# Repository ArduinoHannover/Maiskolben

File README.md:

# Maiskolben

## SMD Lötstation, kompatibel zu Weller-Lötspitzen

Weller baut seit Jahren *die* Lötstationen für den professionellen Bereich.
Die WMRP/WXRP-Stationen heben sich durch ihre aktiven Lötspitzen von anderen Produkten ab.
Mit einer außergewöhnlich kurzen Aufheizzeit im Sekundenbereich, einer direkt in der Spitze integrierten Temperaturmessung und dementsprechend schnelle Nachregulierung in Sekundenbruchteilen sind die Spitzen in der Industrie äußerst beliebt.
Die Spitzen selbst sind für 40€ im Handel erhältlich, die original Weller-Station kostet an die 600€.
Für den einfachen Maker oder Hobbyist auf keinen Fall ein Produkt, das beim Onlineshopping ohne weitere Überlegungen in den Warenkorb wandert.
Der *Maiskolben* hingegen ist eine erschwingliche Lösung für lediglich 40€, mit der die Spitzen ebenso angesteuert werden können.

* Betrieb mit 12V Netzteil (oder bis zu 24V mit Fertigplatine) oder 3s LiPo (Modellbau-Akku)
* Spannungsüberwachung (bei Akku für alle 3 Zellen und automatische Abschaltung bei zu geringer Ladung)
* Einfaches Wechseln von Spitzen mittels Klinken-Buchse/-Kabel
* 3 individuelle Temperatur-Presets
* Temperaturbereich von 200-450°C
* Gut ablesbares Farbdisplay mit allen nötigen Informationen
* Auto-Standby (entweder sensor- oder zeitgesteuert auf 150°C)
* Auto-Wakeup (entweder sensorgesteuert oder durch Berühren von Lötschwamm, Messingwolle oder Lötstelle)
* USB-Schnittstelle zur Überwachung oder Steuerung mittels PC
* Potentialausgleich-/ESD-Buchse (über 1MΩ an GND)
* Optisches Feedback der Heizleistung durch LED
* Open-Source-Software auf Basis von Arduino
* Software-Update kann per USB eingespielt werden

*Zu erwerben bei [HannIO](https://hannio.org).*

## Stromzufuhr

Die Stromzufuhr wird wahlweise über die Hohlstecker-Buchse (10-24V) *ODER* die JST-XH4 (11,1V) Buchse angeschlossen.
Bei Versionen < 3.0 niemals beide gleichzeitig anschließen!
Der Lötkolben (Weller RT-XX, z.B. RT-1 für feine Lötarbeiten) wird über die Klinkenbuchse mit einer Verlängerung angesteckt.

## Display

Das Display zeigt mittig in weißer Schrift die Soll-Temperatur, darunter, sofern eine Spitze eingesteckt ist, die aktuelle Ist-Temperatur.
Bei eingeschaltetem Lötkolben erscheint zusätzlich noch die Zeit, nach der sich der Lötkolben automatisch in den Standby versetzt.
Der Balken am oberen Bildschirmrand spiegelt die Ist-Temperatur wieder.
Oben Links wird die Spannung bzw. die Ladezustände der einzelnen Zellen angezeigt.
Links wird durch das Power-Symbol der aktuelle Zustand (aus = rot, Standby = gelb, an = grün) signalisiert.
Am unteren Rand sind die drei Presets zu sehen.

## Bedienung

Nach dem Anstecken von Netzteil und Lötspitze kann die Station durch halten der Power-Taste (unten rechts) eingeschaltet werden.
Basierend auf der letzten Einstellung wird die angezeigte Soll- (Power-Symbol grün) oder die Standby-Temperatur (Symbol gelb) angefahren.

Mittels der Tasten rechts vom Display (Pfeile) lässt sich die Soll-Temperatur nach oben und unten korrigieren.
Sollte einer der Pfeile auf dem Display ausgegraut sein, so lässt sich über diese Temperatur hinaus keine weitere Änderung mehr vornehmen (200 ≥ T ≥ 450).

### Presets

Mittels der Preset-Tasten unter dem Bildschirm lassen sich voreingestellte Temperaturen als Soll-Temperatur setzen und die Station gleichzeitig aus dem Standby aufwecken.
Durch Gedrückthalten einer der drei Tasten wird der dort gespeicherte Wert durch die aktuelle Soll-Temperatur überschrieben.
Wird die Power-Taste nur kurz gedrückt, so wird der Standby-Zustand umgeschaltet.

### Startmenü

Es gibt ein verstecktes Menü, in dem sich der automatische Standby abschalten und ein automatisches Hochfahren auf die zuletzt gewählte Temperatur bei Spannungsversorgung aktiviert werden können. Um in dieses Menü zu gelangen, muss beim Anlegen der Spannungsversorgung während des Blinkens der LED die Power-Taste betätigt werden.

## Fehlermeldungen

#### USB power only/Connect power supply; Power too low/Connect power >5V
Die Lötstation wird entweder nur über USB oder eine Spannungsquelle mit knapp 5V versorgt.
Zum Betrieb wird ein adäquates Netzteil oder Akku benötigt (≥40W)

#### NO TIP; No tip connected/Tip slipped out?
Es wurde keine Spitze eingesteckt oder nicht erkannt.
Es kann sein, dass die Spitze defekt ist oder nicht richtig in der Buchse steckt.

#### Temperature dropped/Tip slipped out?
Es wurde ein zu großer Temperaturabfall bemerkt und die Wahrscheinlichkeit besteht, dass die Spitze leicht aus der Buchse herausgerutscht ist.
Durch das Herausrutschen kann eine Verbindung zwischen Masse und dem Sensor hergestellt werden, sodass die erkannte Temperatur beim Offset von 24°C liegt.

#### Not heating/Weak power source or short
Entweder kann die Stromversorgung nicht genug Leistung bringen, um die Spitze in einem angemessenen Zeitraum aufzuheizen oder es liegt wie bei obigem Fehler ein Kurzschluss von Masse und Sensor vor.

#### Battery low/Replace or charge
Der Akku hat auf mindestens einer Zelle eine zu geringe Spannung und sollte ersetzt oder geladen werden.

Fehlermeldungen müssen durch OK bestätigt werden.
Die Fehlermeldungen können nicht unterdrückt werden, sollte allerdings mehrfach hintereinander eine Meldung bestätigt und die Station wieder eingeschaltet werden, kann dies zu übermäßigem Erwärmen der Lötspitze führen.

## Software-Update

Um die aktuellste Software auf den Maiskolbe zu übertragen, muss zunächst die [Arduino-IDE](https://www.arduino.cc/en/Main/Software) heruntergeladen werden.
In diesem Repository befinden sich zwei Programme, zum einen Maiskolben_LCD für die Hardware-Revision 1.0 und Maiskolben_TFT für Hardware-Revisionen ab 1.5.
Die .ino Datei kann mit Arduino geöffnet werden.
Der Serielle-Port muss nach Herstellen einer Verbindung zwischen Maiskolben und PC unter _Werkzeuge_ > _Port_ ausgewählt werden.
Unter Umständen muss zuvor noch der [CH340 Treiber](http://www.wch.cn/download/CH341SER_ZIP.html) für den USB-Seriell-Wandler installiert werden.
Als _Board_ sollte _Arduino Nano_ mit _Prozessor: ATmega328 (Old Bootloader)_ ausgewählt werden.
Über _Sketch_ > _Hochladen_ bzw. den Pfeil nach Rechts in der oberen Leiste kann das Programm übertragen werden.

### Bibliotheken

Unter Umständen müssen vorher folgende Libraries noch über _Sketch_ > _Bibliothek einbinden_ > _.ZIP Bibliothek hinzufügen..._ eingebunden werden:

* [TimerOne](https://github.com/PaulStoffregen/TimerOne)
* [PID_v1](https://github.com/br3ttb/Arduino-PID-Library/)
* ~~[Adafruit_ST7735](https://github.com/adafruit/Adafruit-ST7735-Library)~~ (Software Version < 3.0)
* [TFT_ILI9163C](https://github.com/ArduinoHannover/TFT_ILI9163C)
* [Adafruit_GFX](https://github.com/adafruit/Adafruit-GFX-Library)

Dafür muss von den entsprechenden Seiten zuvor die ZIP heruntergeladen werden.
Diese kann dann in dem Dateibrowser, der sich nach obiger Anleitung öffnet, selektiert werden.

### Changelog

* 3.1
  * Option im Menü eingebaut, um zwischen Fahrenheit und Celsius zu wechseln
  * Bug behoben, der bei falsch initialisiertem EEPROM die Temperaturberechnung nicht richtig ausgeführt hat
* 3.0
  * Geänderte Display-Bibliothek (vgl. [Abschnitt Bibliotheken](#Bibliotheken))
  * Mehr Strings im Flash statt im RAM
  * Anpassungen um einen Maiskolben V3.2 im LiPo-Betrieb vollständig abzuschalten
  * Limitierung der Minimaltemperatur auf 200°C
  * `°C` wird mit bei Soll- und Ist-Temperatur angezeigt
  * Interne Temperatur-Kalibrierung für jeden Maiskolben individuell (bisher nur für Kalibrierung ab Werk)
* 2.8
  * Zeilenhöhe des Balkens ist nun variabel
  * Temperaturen als `#define` gesetzt
  * Temperaturberechnung wieder angepasst
  * EEPROM-Fehler behoben
* 2.7
  * TFT-Reset eingebaut
* 2.6
  * Schreibfehler korrigiert
  * Anpassungen an unterschiedliche Hardwareausführungen verbessert
  * Beim Aufruf des Menüs kommt man nach schließen direkt zum Programm
  * Autopower verfeinert
* 2.5
  * Interne Testroutinen hinzugefügt
  * Anpassung an Hardwarerevision ≥ 3.0
  * Wattanzeige hinzugefügt
* 2.4
  * Spannungsanzeige gegen Steckersymbol getauscht
* 2.3
  * Anpassung an unterschiedliche Display-Treiber (BGR/RGB)
  * Geänderte Temperaturmessung
* 2.1
  * Bidirektionale Steuerung über serielle Schnittstelle
* 2.0
  * Initiale Version für GitHub (TFT)
  * Auto-Standby hinzugefügt
  * Parameter angepasst

### Achtung!

Zur eigenen Sicherheit vor einem Software-Update die Lötspitze entfernen.
Zwar wird die Heizspannung beim Übertragen deaktiviert, dennoch kann es vereinzelt zu Fehlfunktionen und dadurch bedingtem unbeschränkten Aufheizen der Spitze kommen.

Modifikationen an der Software sind auf eigene Gefahr des Nutzers.

## Umbauten

Nachfolgend werden Modifikationen beschrieben, die die Funktionen des Maiskolben erweitern.
Für eigens durchgeführte Änderungen kann keine Haftung übernommen werden.

### Ablage-Sensor nachrüsten

Statt des automatischen Standbys nach einer bestimmten Zeit kann auch der Standby durch einen Ablage-Sensor erzwungen werden.
Auf der Platine befinden sich Kontakte mit STBY, 5V und GND.
Um den Standby zu aktivieren muss STBY mit GND verbunden werden, um wieder aufzuwachen muss die Verbindung getrennt werden.
Das Schalten von STBY nach GND kann entweder durch einen Schalter erfolgen, der beim auflegen der Spitze auslöst, alternativ mit einem Hall- oder Reed-Sensor.
Für letzteres muss an dem Ende des Klinken-Kabels, an dem die Spitze eingesteckt wird, ein Magnet angebracht werden, der den Sensor dann auslöst.

### Stromversorgungs-Schalter

Ab Hardware-Revision 1.5 gibt es auf der Platinenunterseite eine Lötbrücke mit der Beschriftung ON/OFF.
Bis einschließlich Revision 1.9 wird beim Durchtrennen dieser Brücke die gesamte Stromversorgung unterbrochen.
Ab Revision 1.11 wird hingegen nur noch die Zuleitung des LiPos getrennt.
An den beiden Lötpunkten können nach dem Durchtrennen der Leiterbahn Kabel zu einem Schalter gelötet werden, mit dem sich die Stromversorgung unterbrechen lässt.

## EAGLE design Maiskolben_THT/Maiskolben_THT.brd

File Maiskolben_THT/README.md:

# Maiskolben-Selfmade

## Selbstbau-Version des Maiskolben mit THT-Bauteilen

Die in diesem Ordner abgelegten Dateien sind für den Nachbau des Maiskolben mit THT-Bauteilen für die Make 5/16.

### Bauteile

| Menge | Bauteil |
---: | ---
1 | 2N700
1 | IRF5305
1 | OPA703PA (OPA336PA)
1 | 74HC4050
1 | Arduino Nano (o.vgl.)
1 | LED 5mm
1 | 220Ω (oder anderer passender Vorwiderstand für die LED)
1 | 100Ω
1 | 1kΩ
2 | 5k6Ω
5 | 10kΩ
1 | 68kΩ
1 | 100kΩ
1 | 10MΩ
2 | 100nF
2 | 10nF
ggf. | Buchsenleisten nach Bedarf
6 | Taster 6x6mm; möglichst hoch (12mm)
1 | Stereo Klinkenbuchse (EBS 35)
1 | DC Buchse (Netzteilspezifisch etwa Lumberg NEB21R)
1 | Passendes Netzteil
1 | Weller Lötspitze

Ein Großteil der Bauteile sind beim Elektronikeinzelhandel verfügbar, das Display hingegen fast ausschließlich bei [eBay](http://sndstrm.de/18tft) bestellbar (sofern nicht mehr verfügbar nach `1.8 tft` suchen, blaue Platine, **nicht** Adafruit), die [Platine oder das ganze Set kann ebenfalls online bestellt werden](https://hannio.org/produkt/maiskolben-tht/).

## Aufbau

Der MOSFET (IRF5305) kann unter das Display gebogen werden, dazu vorher etwas mit Klebeband isolieren, um Kontakt zu vermeiden. Den 2N7000 dafür weit genug versenken.

## Software

Für die Software bitte [die Update-Anleitung](https://github.com/ArduinoHannover/Maiskolben#software-update) zur Hilfe nehmen.

## Problembehandlung

### Display bleibt weiß
In diesem Fall arbeitet der Reset vom Display nicht sauber. Softwareseitig ist dafür `#define USE_TFT_RESET` vorgesehen. Um einen Reset vom Arduino zu triggern, muss allerdings die Reset-Leitung zwischen Arduino und Display getrennt werden.

Bei neueren Platinen gibt es dafür einen Jumper `R A` - dieser ist standardmäßig an R (Reset) angeschlossen. Diese Verbindung muss etwa mit einem Cutter aufgetrennt werden und dann eine Brücke an `A` gesetzt werden.

Ansonsten muss die Leiterbahn aufgekratzt werden oder brutal der Reset-Pin am Arduino weggeknipst werden. Dann muss die Leiterbahn zum Display mit A0 vom Arduino verbunden werden.

### Display zeigt Artefakte
Teilweise arbeitet der Spannungsregler nicht zufriedenstellend, sodass der Treiber des TFT ab und zu Spikes bekommt. In diesem Fall sollten verschiedene Kondensatoren (100nF sollte klappen) am Display VCC/GND oder auch zwischen GND und 5V ein größerer Kondensator (100uF/6,3V) eingebaut werden.

### Andere Probleme

[Fehlermeldungen](https://github.com/ArduinoHannover/Maiskolben#fehlermeldungen)

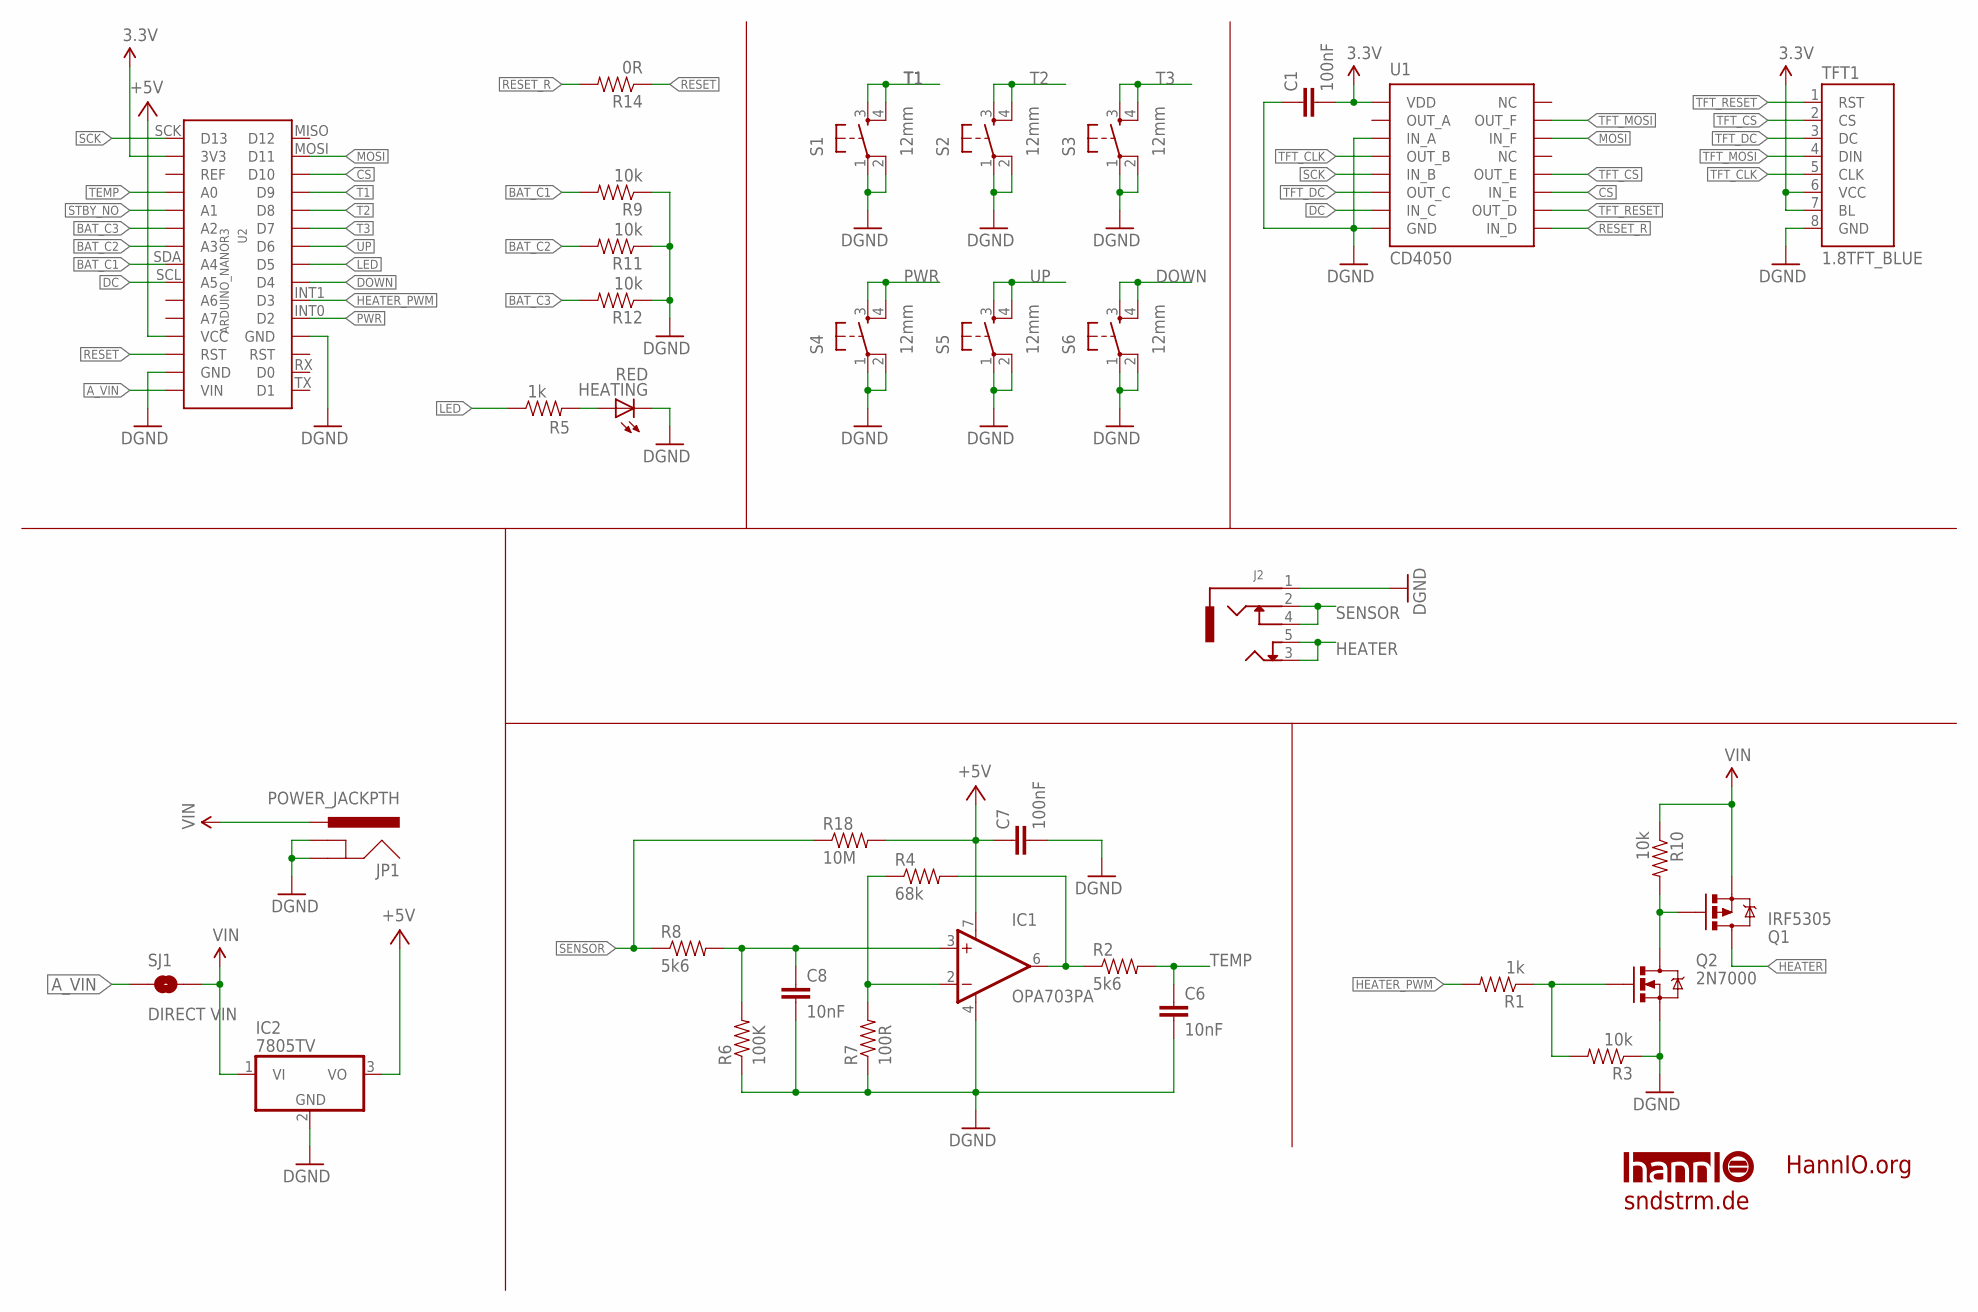
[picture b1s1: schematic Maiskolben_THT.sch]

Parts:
C1, C7: 100nF; CAP-PTH-SMALLEZ
C6, C8: 10nF; CAP-PTH-SMALLEZ
HEATING: RED; LED5MM
IC1: OPA703PA; DIL08
IC2: 7805TV; TO220V
J2: AUDIO_JACK_5PEBS_35; EBS_35
JP1: POWER_JACKPTH; POWER_JACK_PTH
Q1: IRF5305; TO220V
Q2: 2N7000; TO-92
R1, R5: 1k; AXIAL-0.3
R2, R8: 5k6; AXIAL-0.3
R3, R9, R10, R11, R12: 10k; AXIAL-0.3
R4: 68k; AXIAL-0.3
R6: 100K; AXIAL-0.3
R7: 100R; AXIAL-0.3
R14: 0R; AXIAL-0.3
R18: 10M; AXIAL-0.3
S1, S2, S3, S4, S5, S6: 12mm; TACTILE-PTH
SJ1: DIRECT VIN; PAD-JUMPER-2-NO_YES_SILK
TFT1: 1.8TFT_BLUE
U1: CD4050DIP16; CD4050
U2: ARDUINO_NANOR3; ARDUINO-NANO
U$1: HANNIO_MEDIUM

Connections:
3.3V: C1.2, TFT1.6 (VCC), TFT1.7 (BL), U1.VDD, U2.3V3
+5V: C7.1, IC1.7 (V+), IC2.3 (VO), R18.P$2 (2), U2.VCC
A_VIN: SJ1.1, U2.VIN
BAT_C1: R9.P$2 (2), U2.SDA (A4)
BAT_C2: R11.P$2 (2), U2.A3
BAT_C3: R12.P$2 (2), U2.A2
CS: U1.IN_E, U2.D10
DC: U1.IN_C, U2.SCL (A5)
DGND: C1.1, C6.2, C7.2, C8.2, HEATING.K (C), IC1.4 (V-), IC2.2 (GND), J2.1 (GND), JP1.GND, JP1.GNDBREAK, Q2.1 (S), R3.P$1 (1), R6.P$1 (1), R7.P$1 (1), R9.P$1 (1), R11.P$1 (1), R12.P$1 (1), S1.1, S1.2, S2.1, S2.2, S3.1, S3.2, S4.1, S4.2, S5.1, S5.2, S6.1, S6.2, TFT1.8 (GND), U1.GND, U1.IN_A, U2.GND@1 (GND), U2.GND@2 (GND)
DOWN: S6.3, S6.4, U2.D4
HEATER: J2.3 (TIP), J2.5 (TIP_NC), Q1.2 (D)
HEATER_PWM: R1.P$2 (2), U2.INT1 (D3)
HEAT_LED: HEATING.A, R5.P$2 (2)
LED: R5.P$1 (1), U2.D5
MOSI: U1.IN_F, U2.MOSI (D11)
unnamed: Q2.2 (G), R1.P$1 (1), R3.P$2 (2)
OPA+: C8.1, IC1.3 (+IN), R6.P$2 (2), R8.P$2 (2)
OPA-: IC1.2 (-IN), R4.P$1 (1), R7.P$2 (2)
OPA_OUT: IC1.6 (OUT), R2.P$1 (1), R4.P$2 (2)
PMOS_IN: Q1.1 (G), Q2.3 (D), R10.P$2 (2)
PWR: S4.3, S4.4, U2.INT0 (D2)
RESET: R14.P$1 (1), U2.RST@2 (RST)
RESET_R: R14.P$2 (2), U1.IN_D
SCK: U1.IN_B, U2.SCK (D13)
SENSOR: J2.2 (RING), J2.4 (RING_NC), R8.P$1 (1), R18.P$1 (1)
STBY_NO: U2.A1
T1: S1.3, S1.4, U2.D9
T2: S2.3, S2.4, U2.D8
T3: S3.3, S3.4, U2.D7
TEMP: C6.1, R2.P$2 (2), U2.A0
TFT_CLK: TFT1.5 (CLK), U1.OUT_B
TFT_CS: TFT1.2 (CS), U1.OUT_E
TFT_DC: TFT1.3 (DC), U1.OUT_C
TFT_MOSI: TFT1.4 (DIN), U1.OUT_F
TFT_RESET: TFT1.1 (RST), U1.OUT_D
UP: S5.3, S5.4, U2.D6
VIN: IC2.1 (VI), JP1.PWR, Q1.3 (S), R10.P$1 (1), SJ1.2

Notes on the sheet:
HannIO.org
sndstrm.de

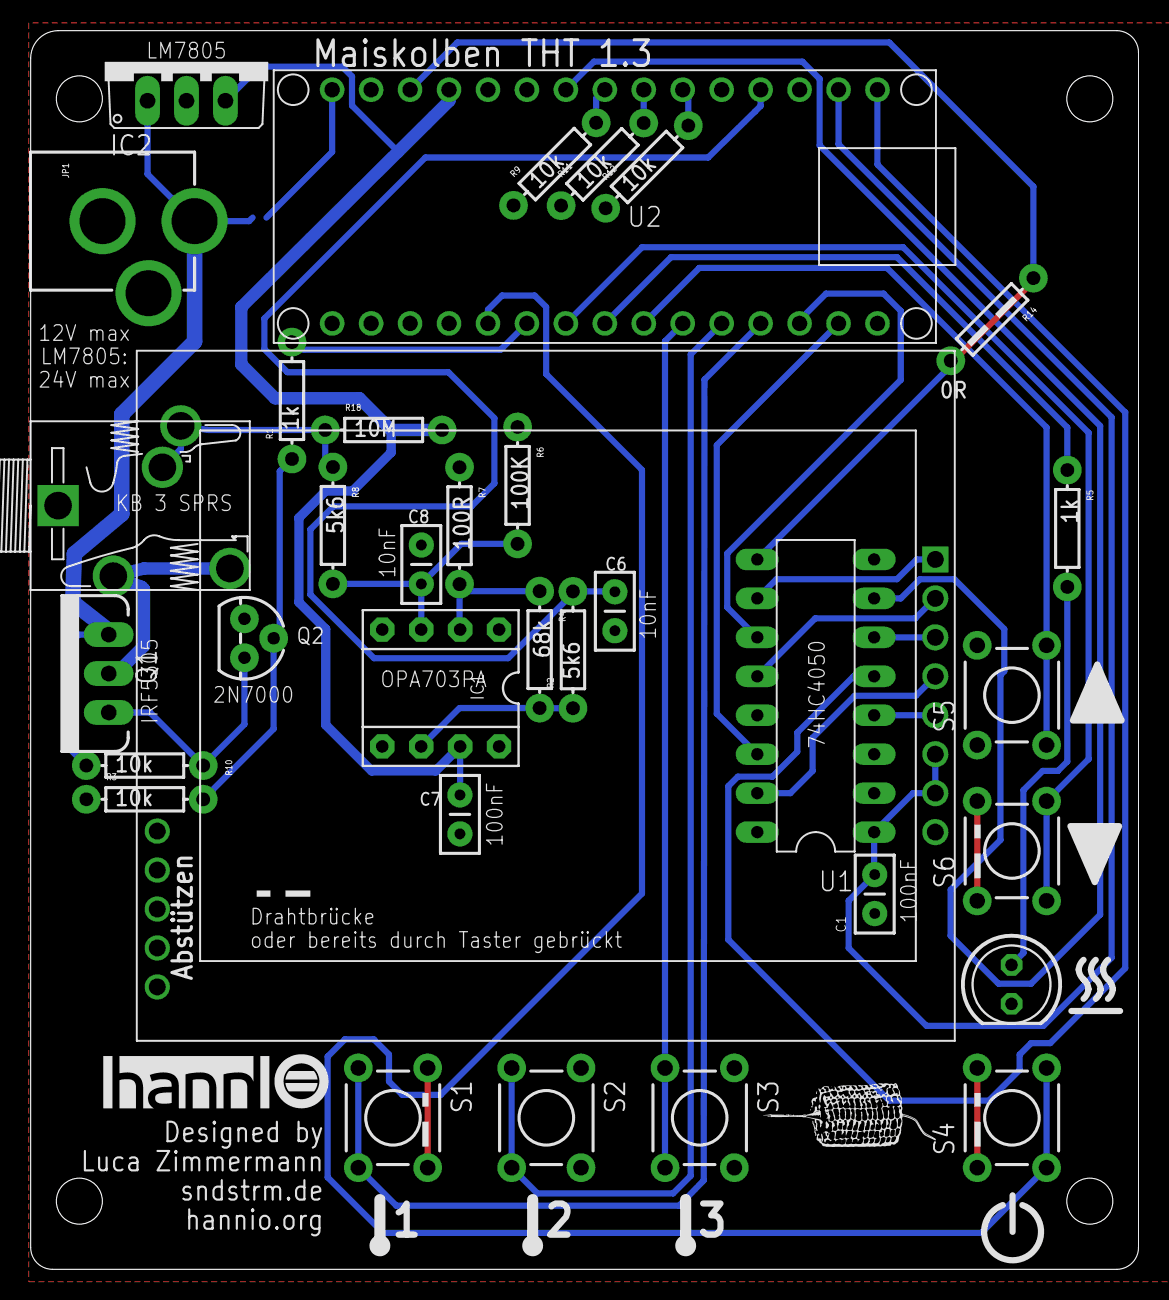
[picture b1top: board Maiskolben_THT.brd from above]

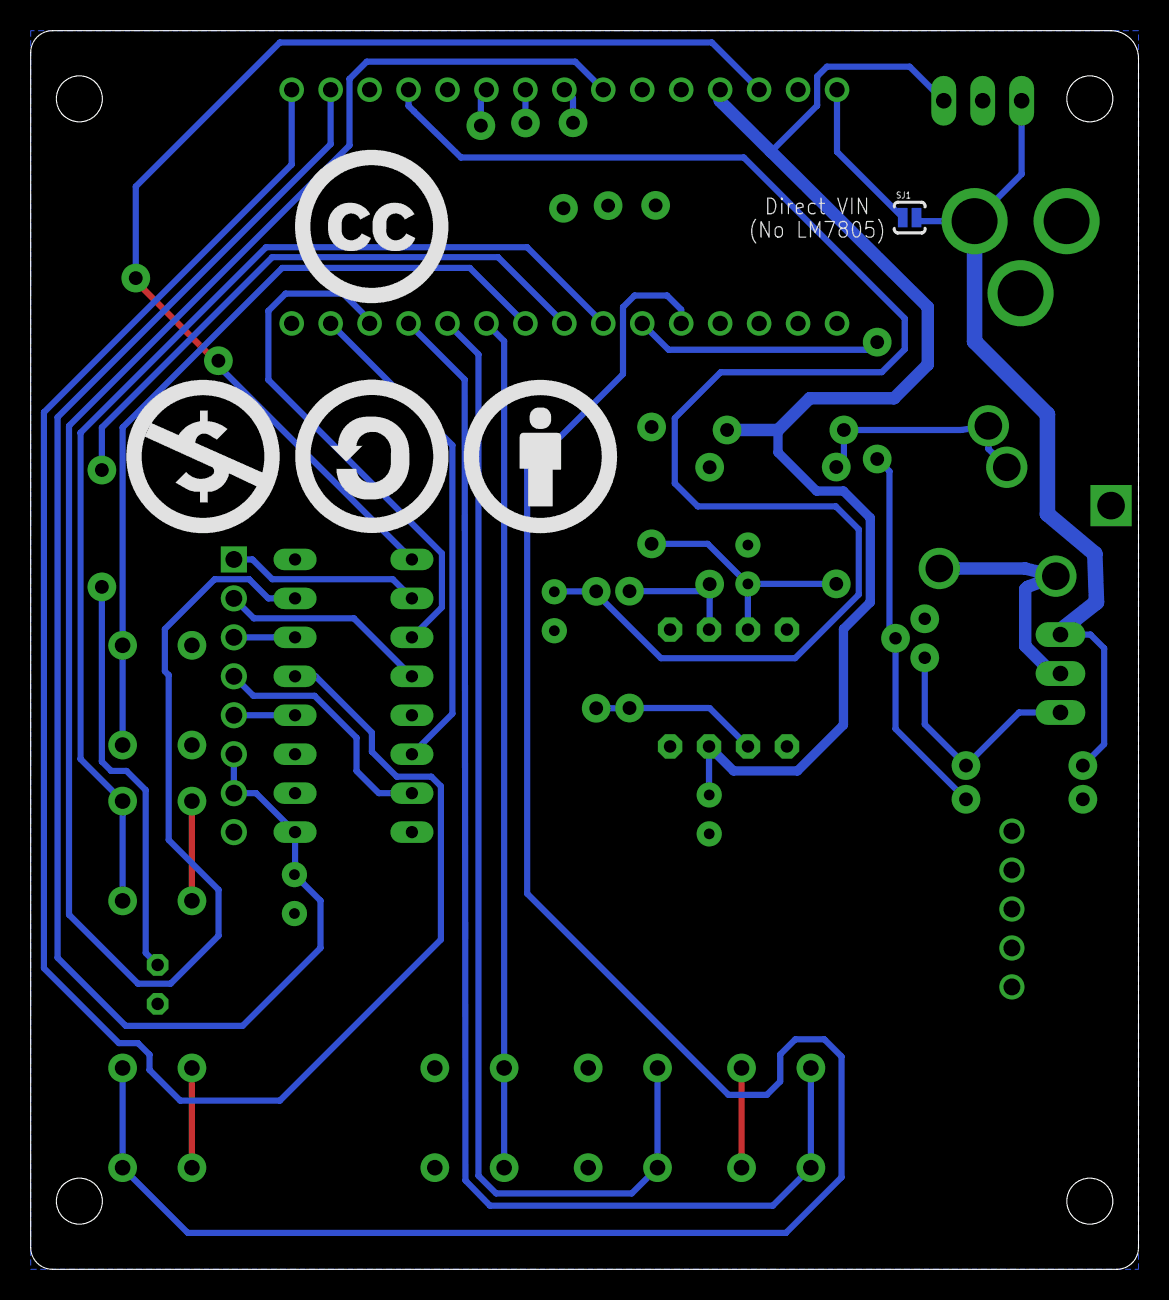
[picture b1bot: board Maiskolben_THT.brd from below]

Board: 2 copper layers, 72.2 x 80.8 mm, 41 parts (5 on the bottom side), 36 nets.

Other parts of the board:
U$2: MAISKOLBEN
U$4: BY_TPLACE
U$5: SA_TPLACE
U$6: NC_TPLACE
U$7: CC_TPLACE

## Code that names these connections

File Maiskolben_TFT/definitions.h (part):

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//      RX          0
//      TX          1
#define SW_STBY     2
#define HEATER_PWM  3
#define SW_DOWN     4
#define HEAT_LED    5
#define SW_UP       6
#define SW_T3       7
#define SW_T2       8
#define SW_T1       9
#define TFT_CS      10
//      MOSI        11
#define POWER       12 //use MISO PULLUP as switch
//      SCK         13
#define TEMP_SENSE  A0
#define STBY_NO     A1
#define BAT_C3      A2
#define BAT_C2      A3
#define BAT_C1      A4
#define TFT_DC      A5
#ifdef PIN_A7
#define CHARGEDET   A6
#define VIN         A7
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
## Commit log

2016-02-05 supports splash screen at start up
2016-02-05 date correction
2016-02-05 spelling mistake
2016-02-06 corrected line numbering
2016-05-30 Version 2.0
2016-05-30 Small modifications
2016-06-23 Version 2.1
    GUI not working with 2.1
2016-06-23 Forgot OFF_TIMOUT
2016-09-28 Upgrade to 2.3
    Compatibility for new displays - if you upgrade you will be asked if
    the screen shows blue or red.
    Improved the temperature measurement, the 100k pulldown altered the
    measurement, so the temperature was 30-50°C hotter than measured.
    Based on this measurement error, you can now officially set the max
    temperature of 450°C.
2016-10-08 Added Maiskolben DIY, Case and 2.4 Update
    Added Gerber- and Eagle-Files for DIY-Maiskolben, Lasercut-Files for
    Maiskolben TFT (DIY Case is in progress) and upgraded Software to 2.4:
    Changed display of DC input to power cord, which will change from red
    (< 12V) to green (> 14.5V) to symbolize a good power supply and
    circumvent the wrong displayed voltage by voltage-divider with a
    maximum measurable VIN of 14.79 V. Therefore added a power cord icon.
2016-10-12 Removed deprecated Maiskolben_LCD
2016-11-02 Fixed 3v3 connection
2016-11-10 Added Displayfix
    A fix to compensate power supply problems (white display on boot)
2016-12-02 Added outline-dxf for Maiskolben (SMD)
2016-12-02 Removed grouping
2016-12-02 Added dxf converted as svg
2016-12-04 Added 3D-File
2016-12-05 Hooray, v2.5
    New temperature measurement (again…), show the effective heat power in
    watts, advanced features for Rev. 3.x (more to come), some private
    features for testing
2017-01-21 Push to SW V2.6
    Minor new features
2017-01-21 Added user manual
2017-01-21 Added gitignore
2017-01-21 Push to HW V1.3
    Closes #3, adds drill file (whoops), adds optional LM7805 for v > 12V
2017-01-24 Reorganized
2017-01-24 Info for Maiskolben THT
2017-03-05 Added Maiskolben THT Case + Spongeholder
    Finally closes #2, but is case currently untested (should be working
    fine...)
2017-03-05 Updated Case
    "Should be working" was the right text - should but wasn't
2017-03-05 Added 3D Model of Lasercut File
    And removed a small edge and added a notch for USB-cables
2017-03-05 Merge dxf to stl
    Added the notch for USB to the sol too
2017-03-09 Referenced TFT-Blank issue, modified notch for case
    Even deeper notch as the USB-Cable has no chance to be plugged in
    otherwise.
    Referenced white-screen issues in Maiskolben_Mechaincal/README.md and
    added a software fix, bump to V2.7
2017-06-01 Refactoring, higher temperature bar, correct EEPROM update
    - EEPROM autoboot/auto shutdown was set to auto shutdown when updating
    temperature
    - Indentation for definition.h altered
    - More constants
    - Better constant names
    - Individual temperature bar height
2017-09-21 Added image
2017-09-27 V3.0
    - Geänderte Display-Bibliothek (vgl. Abschnitt Bibliotheken der Readme)
    - Mehr Strings im Flash statt im RAM
    - Anpassungen um einen Maiskolben V3.2 im LiPo-Betrieb vollständig
    abzuschalten
    - Limitierung der Minimaltemperatur auf 200°C
    - `°C` wird mit bei Soll- und Ist-Temperatur angezeigt
2017-11-30 Added option to set °C or °F; fixed EEPROM issue
    In boot menu you can now choose to display either celsius or farenheit.
    An issue was fixed which loaded illegal values from EEPROM for ADC
    offset and gain.
2017-11-30 Dokumentation update (THT-Teilliste/V3.1)
2018-12-22 Use the real voltage for power calculation, do not assume min of 15V.
2018-12-22 Ensure that the temperature is rising when it should.
    We observerd a strange error yielding in dead tips* we attribute
    to shorts between two contacts on the 3.5 mm connector** (bad cable...)
    and we hope this failure mode will be covered by this feature.
    The feature works by monitoring the temperature and making sure that
    in a certain time a certain temperature rising is seen.
    The tuning can be done by a few parameters:
2018-12-22 Feature: Power limitation
    Weller tips are rated for 40W (at least most of them). On higher input
    voltage, this is exceeded.
    This feature limits it by put a cap on the pwm, dependent on the input
    voltage.
2020-05-03 Update to current values
    Closes #13

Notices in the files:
parts and their libraries:
SparkFun-Aesthetics: Licensing: Creative Commons ShareAlike 4.0 International - https://creativecommons.org/licenses/by-sa/4.0
